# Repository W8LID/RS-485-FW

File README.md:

# RS-485-FW
An RS-485 FeatherWing for the Adafruit Feather system.

The RS-485 FeatherWing provides level shifting of the TTL UART on Adafruit Feather type development boards. This board is based on the Maxim MAX3485 transceiver. It also provides an automatic direction control circuit so as to not require any additional GPIO pins for direction control.

This board is designed with minimal components in mind to keep complexity and cost to a minimum. Component footprints were chosen to allow for hand soldering and no special equipment required for assembly.

Note: The 4.7kΩ bias resistors (R1 & R3) should only be populated on a single device on an RS-485 bus. That is, if attempting to communicate between two RS-485 FeatherWings on the same bus, only populate R1 & R3 on a single FeatherWing.

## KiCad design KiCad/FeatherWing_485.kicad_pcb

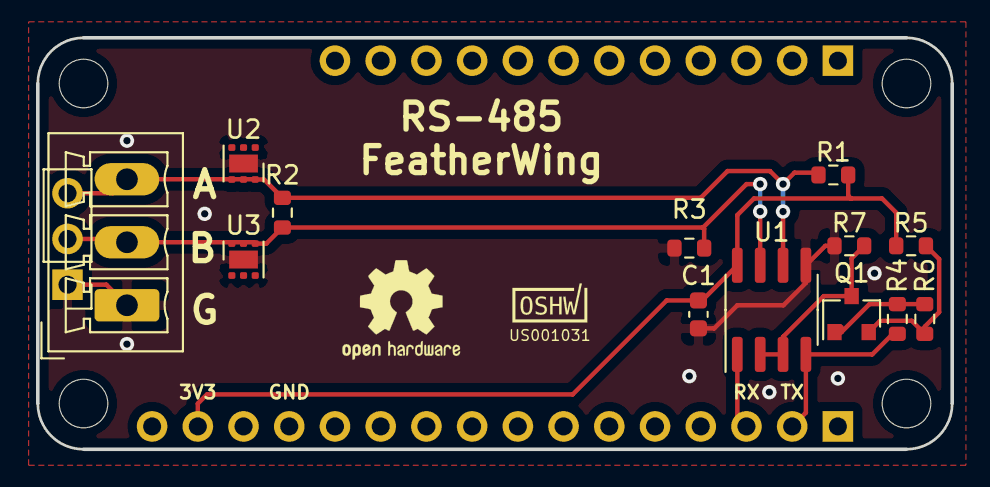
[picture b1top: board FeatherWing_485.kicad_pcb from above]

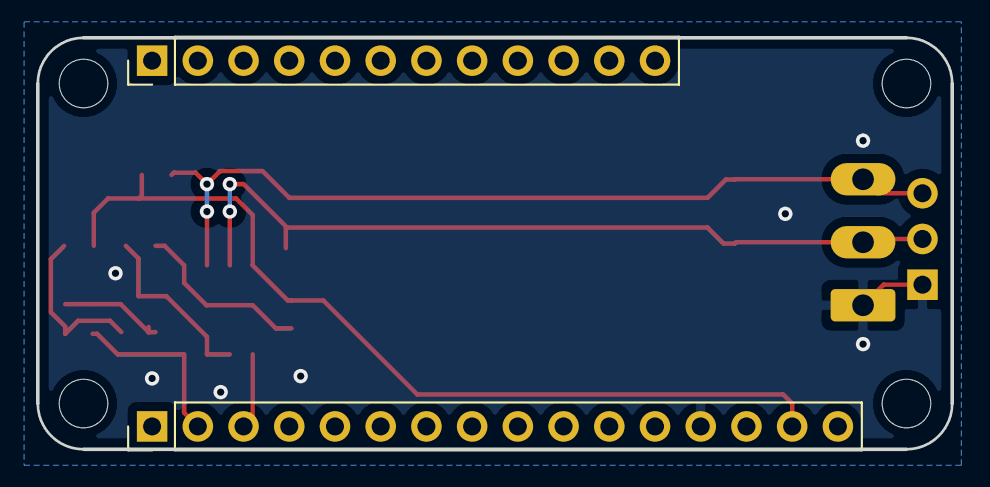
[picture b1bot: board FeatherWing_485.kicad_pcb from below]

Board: 2 copper layers, 50.8 x 22.9 mm, 17 parts (2 on the bottom side), 9 nets.

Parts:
C1: 0.01uF; C_0603_1608Metric
J1: feather long; PinHeader_1x16_P2.54mm_Vertical
J2: feather short; PinHeader_1x12_P2.54mm_Vertical
J3: Screw_Terminal_01x03; PhoenixContact_MCV_1,5_3-G-3.5_1x03_P3.50mm_Vertical
J4: Conn_01x03_Male; PinHeader_1x03_P2.54mm_Vertical
OSHW_Mono_0.1_Scale: US001031; OSHW_Mono_0.1_Scale
Q1: BC857; SOT-23
R1, R3: 4.7k; R_0603_1608Metric
R2: 120; R_0603_1608Metric
R4, R5: 100; R_0603_1608Metric
R6, R7: 2.2k; R_0603_1608Metric
U1: MAX3485; SOIC-8_3.9x4.9mm_P1.27mm
U2, U3: TVS0500DRV; WSON-6-1EP_2x2mm_P0.65mm_EP1x1.6mm

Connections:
+3V3: C1.2, J1.15, R1.1, R5.1, U1.8
/RX: J1.3, U1.1
/TX: J1.2, R4.1, U1.4
GND: C1.1, J1.13, J3.1, J4.1, R3.2, R7.2, U1.5, U2.1, U2.2, U2.3, U2.7, U3.1, U3.2, U3.3, U3.7
unnamed: J3.2, J4.2, R2.2, R3.1, U1.7, U3.4, U3.5, U3.6
unnamed: J3.3, J4.3, R1.2, R2.1, U1.6, U2.4, U2.5, U2.6
unnamed: Q1.1, R4.2, R6.1
unnamed: Q1.2, R5.2, R6.2
unnamed: Q1.3, R7.1, U1.2, U1.3

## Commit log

2020-12-12 Create LICENSE
2020-12-12 Add schematic and PCB renders.
    Add schematic and PCB PDF files as well as a 3D PCB render image.
2020-12-12 Add KiCad files.
    Add KiCad projecct files.
2020-12-12 Update LICENSE
    Use correct license.
2020-12-12 Create LICENSE
    Use correct license
2020-12-12 Fix footprint
    Use 0603 footprint for C1
2020-12-12 Add BOM
    Add BOM generated by KiCad
2020-12-12 Update render
    Changed C1 footprint
2020-12-12 Delete 485-FeatherWing.png
    Wrong file uploaded
2020-12-12 Updated render
    Changed footprint of C1
2020-12-13 Update PCB
2020-12-13 Updated PCB
    Add copper fill.
2021-03-07 Update kicad files
    Update for revised PCB
2021-03-07 Delete PDF version of PCB
    Delete PDF in exchange for PNG
2021-03-07 Update images
    update images for PCB
2021-03-07 Update README.md
    Add board render image
2025-01-07 Add documentation abount multiple FeatherWings on the same RS-485 bus
